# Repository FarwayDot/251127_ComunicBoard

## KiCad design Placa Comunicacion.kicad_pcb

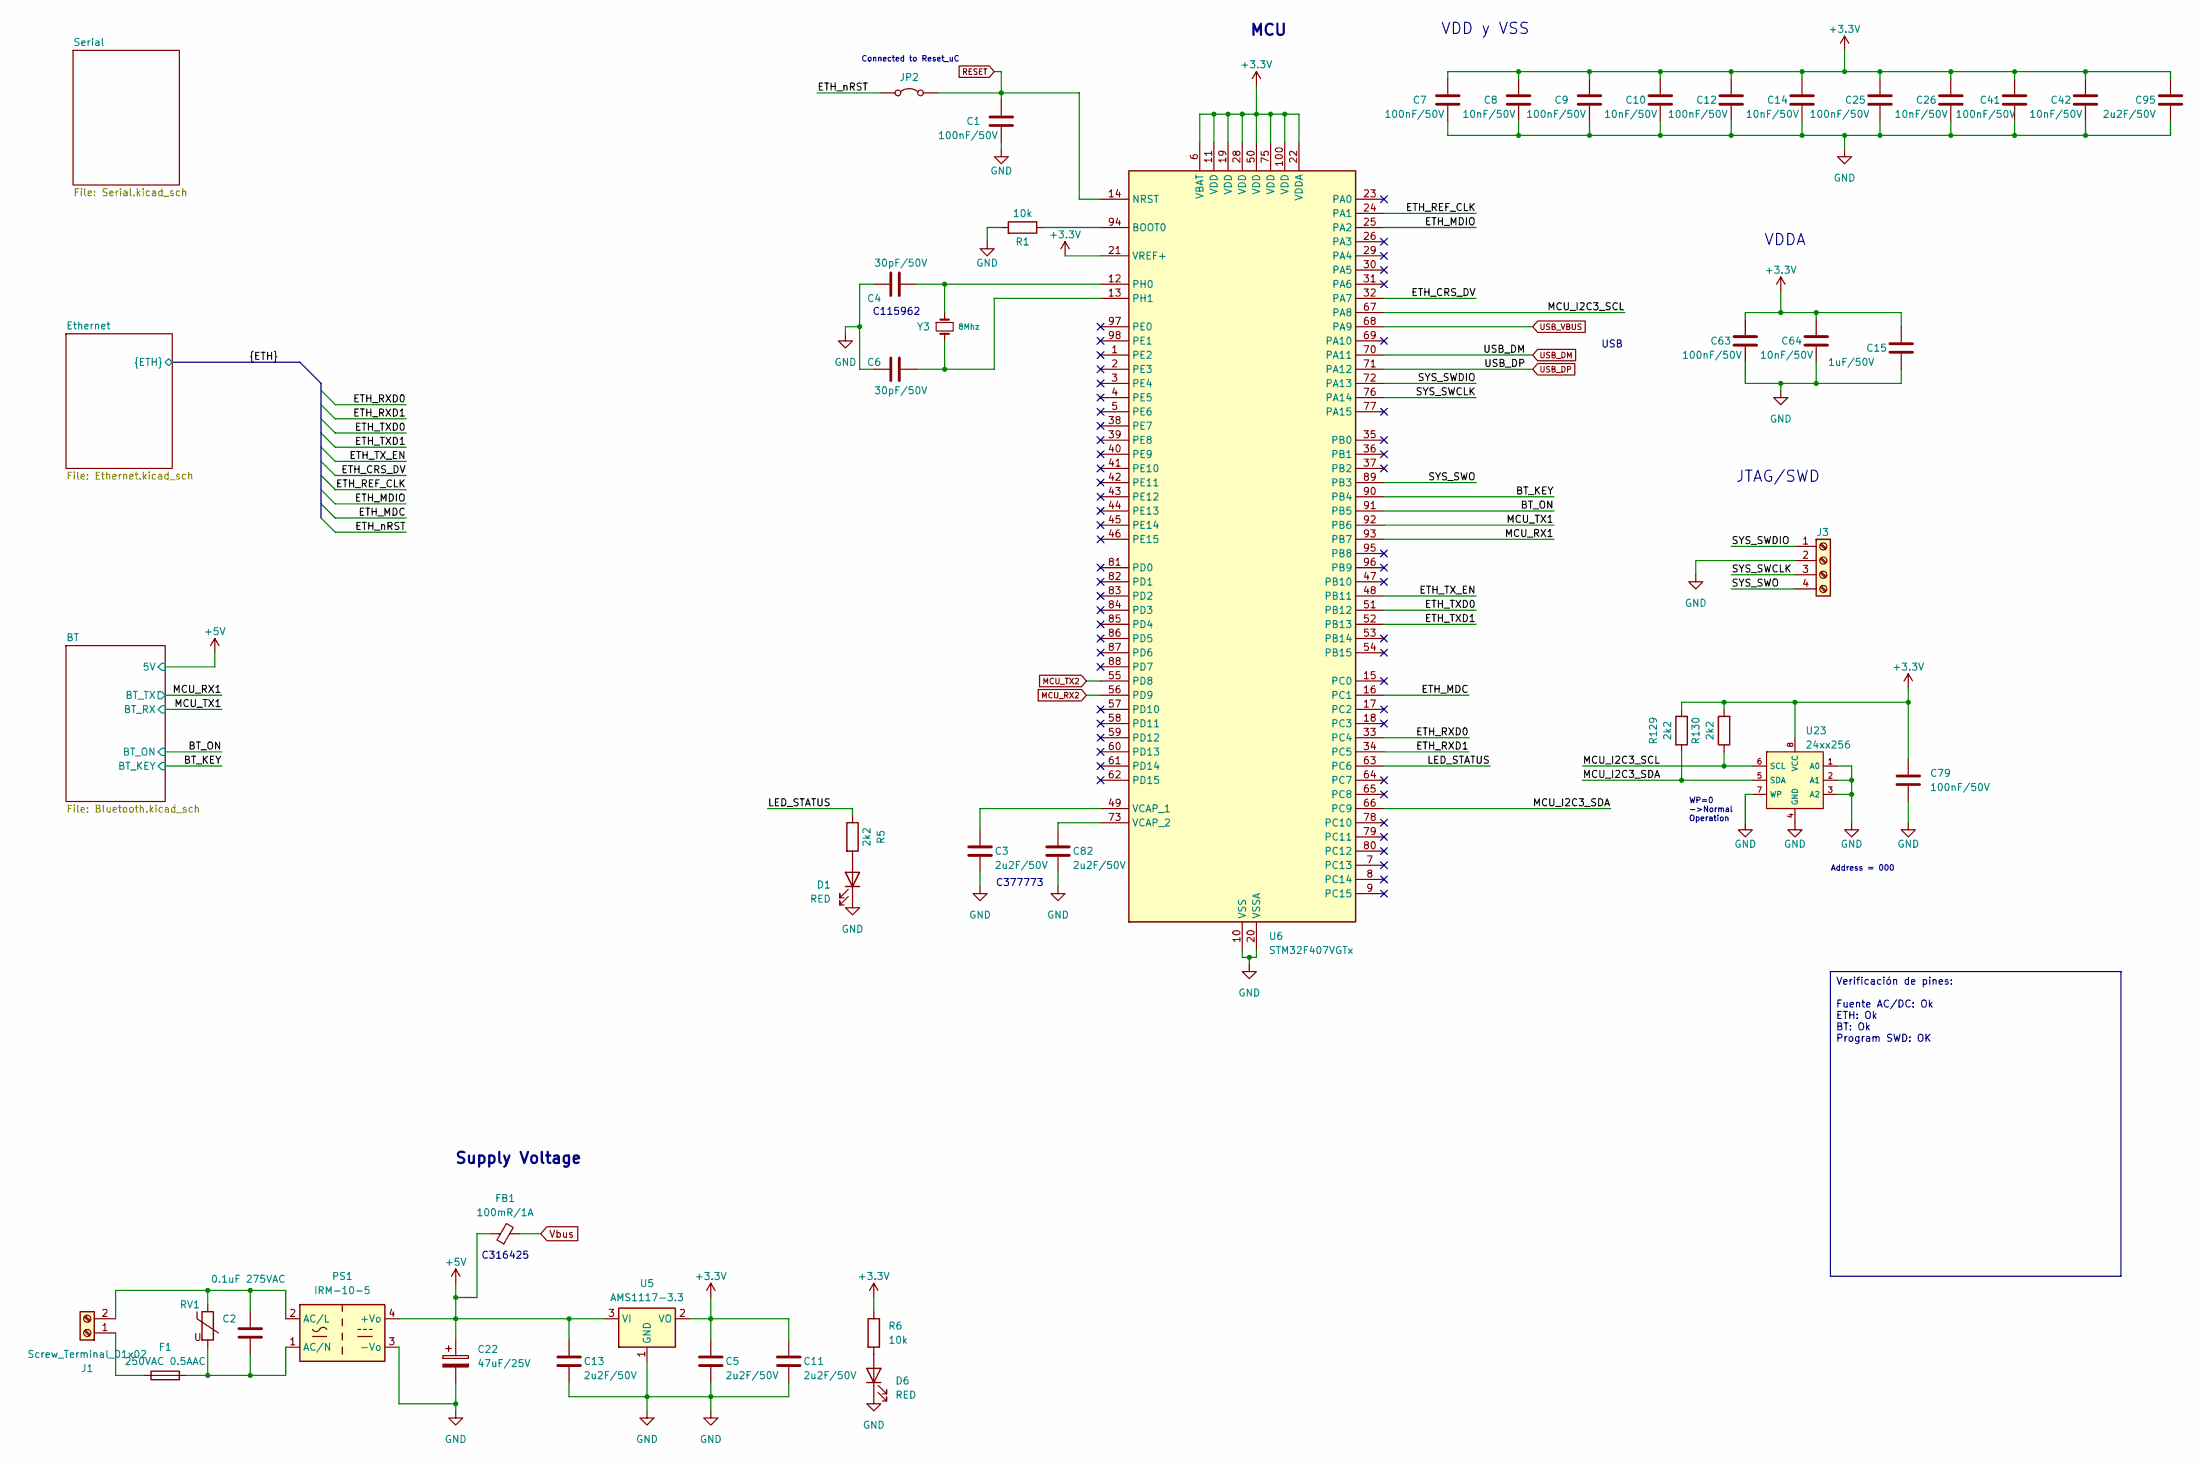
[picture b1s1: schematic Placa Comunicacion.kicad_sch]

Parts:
C1, C7, C9, C12, C25, C41, C63, C79: 100nF/50V; C_0603_1608Metric
C2: 0.1uF 275VAC; C_Rect_L18.0mm_W5.0mm_P15.00mm_FKS3_FKP3
C3, C5, C11, C13, C82, C95: 2u2F/50V; C_0805_2012Metric
C4, C6: 30pF/50V; C_0603_1608Metric
C8, C10, C14, C26, C42, C64: 10nF/50V; C_0603_1608Metric
C15: 1uF/50V; C_0805_2012Metric
C22: 47uF/25V; CP_Radial_D5.0mm_P2.50mm
D1, D6: RED; LED_0805
F1: 250VAC 0.5AAC; Fuseholder_TR5_Littelfuse_No560_No460
FB1: 100mR/1A; L_0805_2012Metric
J1: Screw_Terminal_01x02; DG126_5.0_02P
J3: Screw_Terminal_01x04; PinHeader_1x04_P2.54mm_Vertical
JP2: Jumper_2_Bridged; SolderJumper-2_P1.3mm_Open_Pad1.0x1.5mm
PS1: IRM-10-5; Converter_ACDC_MeanWell_IRM-10-xx_THT
R1, R6: 10k; R_0603_1608Metric
R5, R129, R130: 2k2; R_0603_1608Metric
RV1: RM10D561KD24E100; RV_Disc_D12mm_W5.1mm_P7.5mm
U5: AMS1117-3.3; SOT-223-3_TabPin2
U6: STM32F407VGTx; LQFP-100_14x14mm_P0.5mm
U23: 24xx256; SO-8_3.9x4.9mm_P1.27mm
Y3: 8Mhz; Crystal_SMD_5032-2Pin_5.0x3.2mm

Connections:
+3.3V: C5.1, C7.1, C8.1, C9.1, C10.1, C11.1, C12.1, C14.1, C15.1, C25.1, C26.1, C41.1, C42.1, C63.1, C64.1, C79.1, C95.1, R6.1, R129.2, R130.2, U5.2 (VO), U6.6 (VBAT), U6.11 (VDD), U6.19 (VDD), U6.21 (VREF+), U6.22 (VDDA), U6.28 (VDD), U6.50 (VDD), U6.75 (VDD), U6.100 (VDD), U23.8 (VCC); also elsewhere on the board
+5V: C13.1, C22.1, FB1.1, PS1.4 (+Vo), U5.3 (VI); also elsewhere on the board
/BT_KEY: U6.90 (PB4); also elsewhere on the board
/BT_ON: U6.91 (PB5); also elsewhere on the board
/ETH_CRS_DV: U6.32 (PA7); also elsewhere on the board
/ETH_MDC: U6.16 (PC1); also elsewhere on the board
/ETH_MDIO: U6.25 (PA2); also elsewhere on the board
/ETH_REF_CLK: U6.24 (PA1); also elsewhere on the board
/ETH_RXD0: U6.33 (PC4); also elsewhere on the board
/ETH_RXD1: U6.34 (PC5); also elsewhere on the board
/ETH_TXD0: U6.51 (PB12); also elsewhere on the board
/ETH_TXD1: U6.52 (PB13); also elsewhere on the board
/ETH_TX_EN: U6.48 (PB11); also elsewhere on the board
/ETH_nRST: JP2.1 (A); also elsewhere on the board
/LED_STATUS: R5.1, U6.63 (PC6)
/MCU_I2C3_SCL: R130.1, U6.67 (PA8), U23.6 (SCL)
/MCU_I2C3_SDA: R129.1, U6.66 (PC9), U23.5 (SDA)
/MCU_RX1: U6.93 (PB7); also elsewhere on the board
/MCU_TX1: U6.92 (PB6); also elsewhere on the board
/SYS_SWCLK: J3.3, U6.76 (PA14)
/SYS_SWDIO: J3.1, U6.72 (PA13)
/SYS_SWO: J3.4, U6.89 (PB3)
GND: C1.2, C3.2, C4.2, C5.2, C6.2, C7.2, C8.2, C9.2, C10.2, C11.2, C12.2, C13.2, C14.2, C15.2, C22.2, C25.2, C26.2, C41.2, C42.2, C63.2, C64.2, C79.2, C82.2, C95.2, D1.1 (K), D6.1 (K), J3.2, PS1.3 (-Vo), R1.2, U5.1 (GND), U6.10 (VSS), U6.20 (VSSA), U6.27 (VSS), U6.74 (VSS), U6.99 (VSS), U23.1 (A0), U23.2 (A1), U23.3 (A2), U23.4 (GND), U23.7 (WP); also elsewhere on the board
MCU_RX2: U6.56 (PD9); also elsewhere on the board
MCU_TX2: U6.55 (PD8); also elsewhere on the board
unnamed: D1.2 (A), R5.2
unnamed: D6.2 (A), R6.2
unnamed: F1.1, J1.1
unnamed: C2.1, J1.2, PS1.2 (AC/L), RV1.1
unnamed: C2.2, F1.2, PS1.1 (AC/N), RV1.2
unnamed: R1.1, U6.94 (BOOT0)
unnamed: C4.1, U6.12 (PH0), Y3.1
unnamed: C6.1, U6.13 (PH1), Y3.2
unnamed: C3.1, U6.49 (VCAP_1)
unnamed: C82.1, U6.73 (VCAP_2)
RESET: C1.1, JP2.2 (B), U6.14 (NRST)
USB_DM: U6.70 (PA11); also elsewhere on the board
USB_DP: U6.71 (PA12); also elsewhere on the board
USB_VBUS: U6.68 (PA9); also elsewhere on the board
Vbus: FB1.2; also elsewhere on the board

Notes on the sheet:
C377773
Address = 000
MCU
USB
JTAG/SWD
C316425
Connected to Reset_uC
WP=0 ->Normal Operation
Supply Voltage
C115962
VDD y VSS
VDDA
Verificación de pines: Fuente AC/DC: Ok ETH: Ok BT: Ok Program SWD: OK

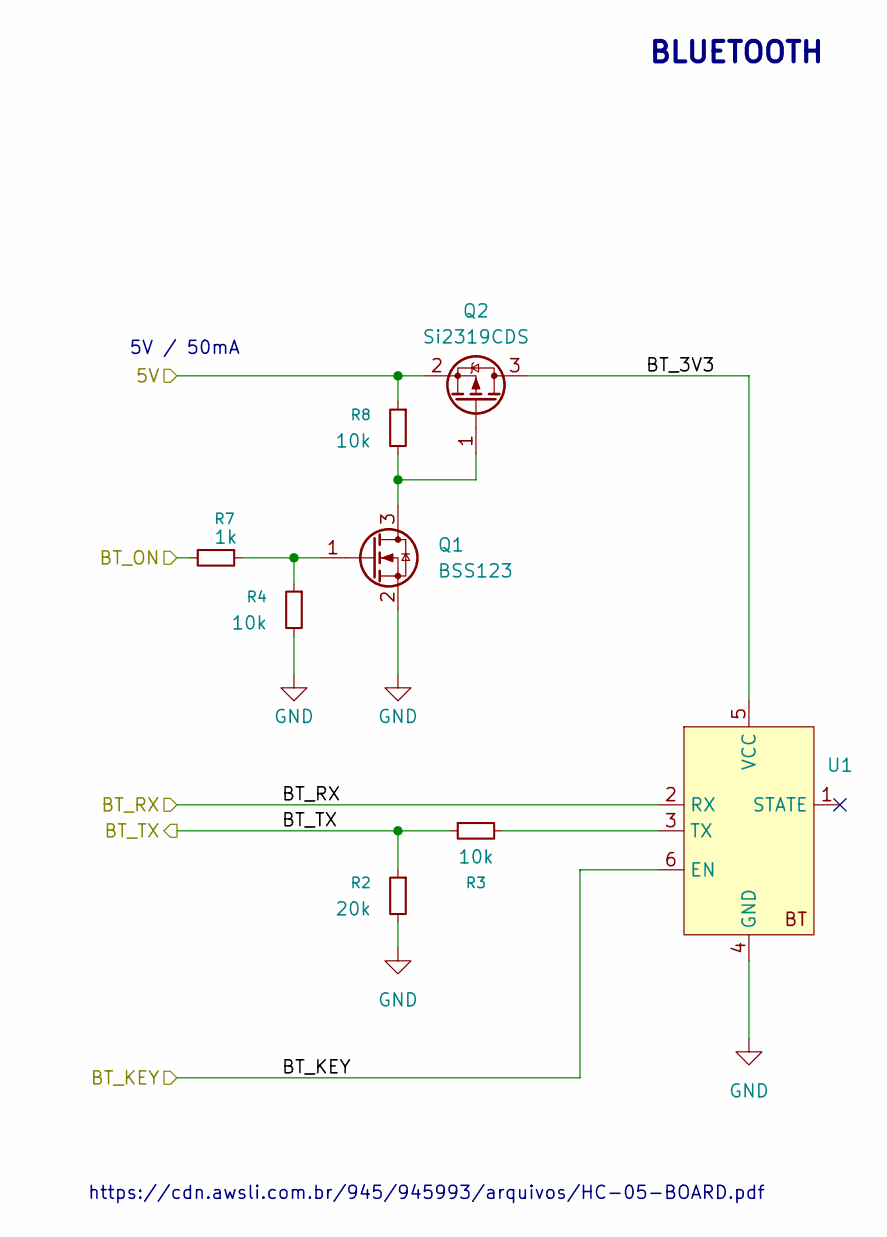
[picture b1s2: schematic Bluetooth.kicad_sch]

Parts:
Q1: BSS123; SOT-23
Q2: Si2319CDS; SOT-23
R2: 20k; R_0603_1608Metric
R3, R4, R8: 10k; R_0603_1608Metric
R7: 1k; R_0603_1608Metric
U1: HC-05

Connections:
+5V: Q2.2 (S), R8.1; also elsewhere on the board
/BT/BT_3V3: Q2.3 (D), U1.5 (VCC)
/BT_KEY: U1.6 (EN); also elsewhere on the board
/BT_ON: R7.2; also elsewhere on the board
/MCU_RX1: R2.1, R3.1; also elsewhere on the board
/MCU_TX1: U1.2 (RX); also elsewhere on the board
GND: Q1.2 (S), R2.2, R4.2, U1.4 (GND); also elsewhere on the board
unnamed: Q1.3 (D), Q2.1 (G), R8.2
unnamed: Q1.1 (G), R4.1, R7.1
unnamed: R3.2, U1.3 (TX)

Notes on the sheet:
https://cdn.awsli.com.br/945/945993/arquivos/HC-05-BOARD.pdf
5V / 50mA
BLUETOOTH

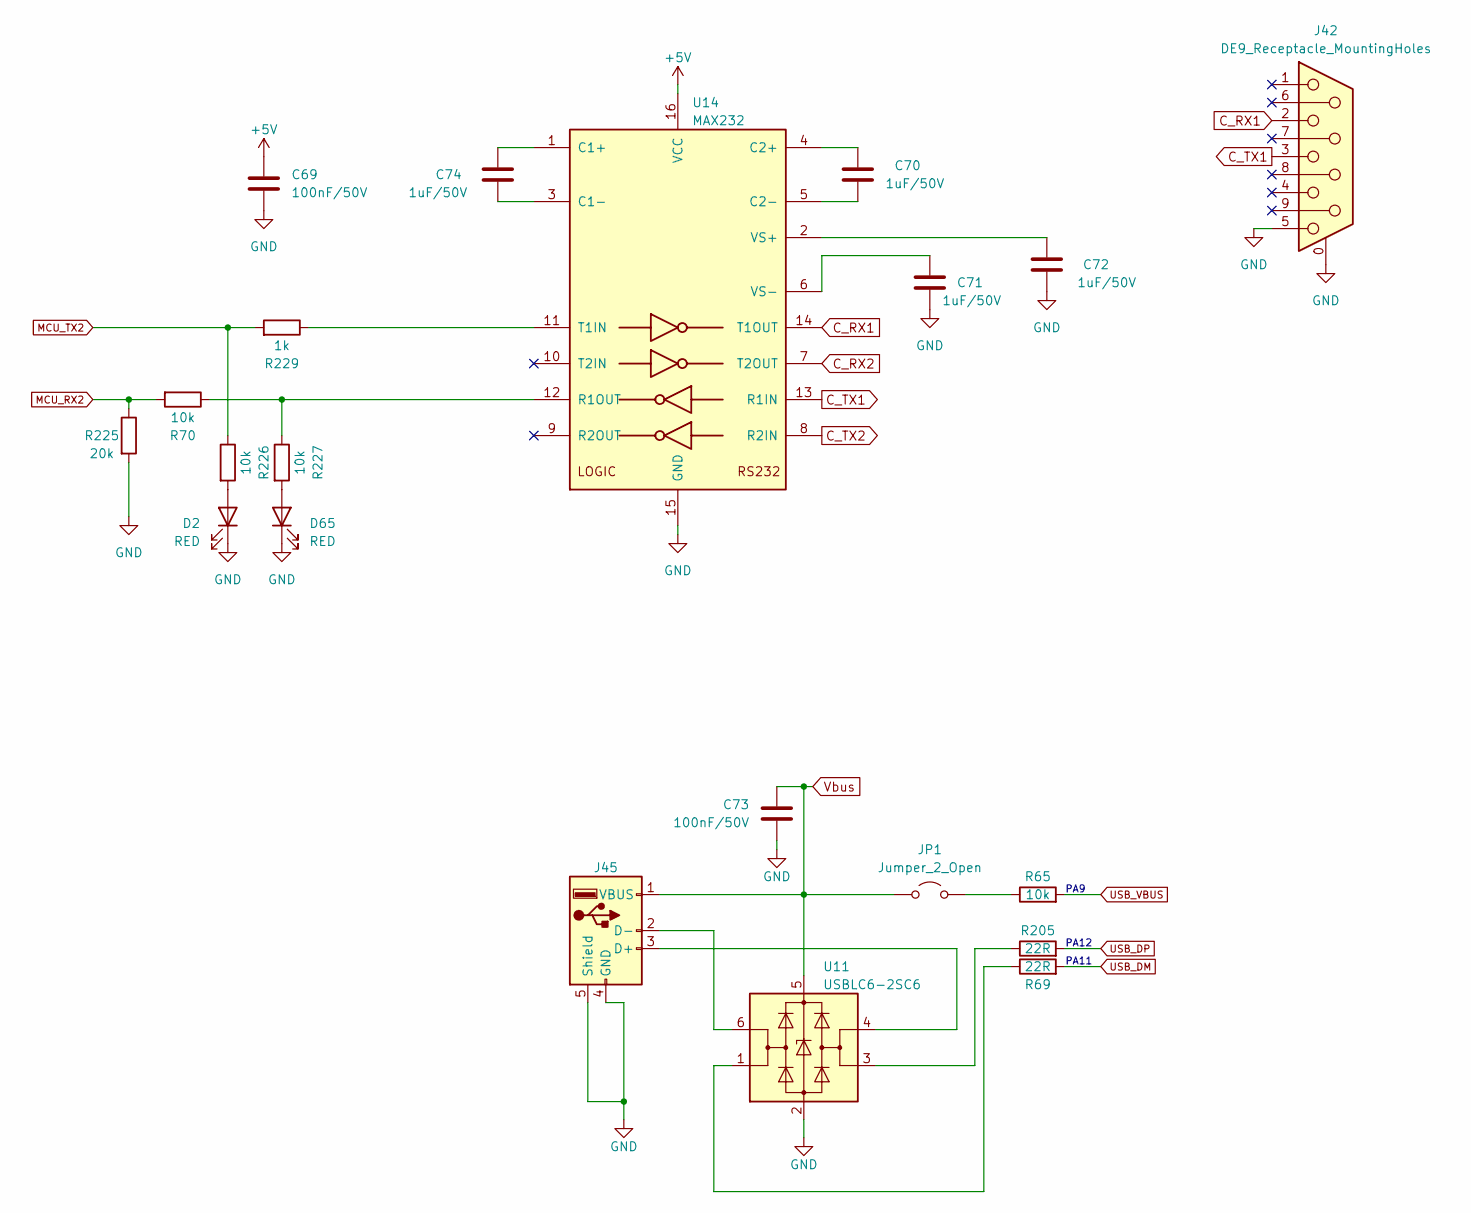
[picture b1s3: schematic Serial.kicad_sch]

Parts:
C69, C73: 100nF/50V; C_0603_1608Metric
C70, C71, C72, C74: 1uF/50V; C_0805_2012Metric
D2, D65: RED; LED_0805
J42: DE9_Receptacle_MountingHoles; DSUB-9_Pins_Horizontal_P2.77x2.84mm_EdgePinOffset7.70mm_Hou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
J45: USB_A_Female_P2.5mm; MOLEX_67329-8020
JP1: Jumper_2_Open; PinHeader_1x02_P2.54mm_Vertical
R65, R70, R226, R227: 10k; R_0603_1608Metric
R69, R205: 22R; R_0603_1608Metric
R225: 20k; R_0603_1608Metric
R229: 1k; R_0603_1608Metric
U11: USBLC6-2SC6; SOT-23-6
U14: MAX232; SOIC-16_3.9x9.9mm_P1.27mm

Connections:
+5V: C69.1, U14.16 (VCC); also elsewhere on the board
C_RX1: J42.2, U14.14 (T1OUT)
C_RX2: U14.7 (T2OUT)
C_TX1: J42.3, U14.13 (R1IN)
C_TX2: U14.8 (R2IN)
GND: C69.2, C71.2, C72.2, C73.2, D2.1 (K), D65.1 (K), J42.0 (PAD), J42.5, J45.4 (GND), J45.5 (Shield), R225.2, U11.2 (GND), U14.15 (GND); also elsewhere on the board
MCU_RX2: R70.2, R225.1; also elsewhere on the board
MCU_TX2: R226.1, R229.2; also elsewhere on the board
unnamed: D2.2 (A), R226.2
unnamed: D65.2 (A), R227.2
unnamed: J45.3 (D+), U11.4 (I/O2)
unnamed: J45.2 (D-), U11.6 (I/O1)
unnamed: JP1.2 (B), R65.1
unnamed: R69.1, U11.1 (I/O1)
unnamed: R205.1, U11.3 (I/O2)
unnamed: C74.1, U14.1 (C1+)
unnamed: C74.2, U14.3 (C1-)
unnamed: C70.1, U14.4 (C2+)
unnamed: C70.2, U14.5 (C2-)
unnamed: R70.1, R227.1, U14.12 (R1OUT)
unnamed: R229.1, U14.11 (T1IN)
unnamed: C72.1, U14.2 (VS+)
unnamed: C71.1, U14.6 (VS-)
USB_DM: R69.2; also elsewhere on the board
USB_DP: R205.2; also elsewhere on the board
USB_VBUS: R65.2; also elsewhere on the board
Vbus: C73.1, J45.1 (VBUS), JP1.1 (A), U11.5 (VBUS); also elsewhere on the board

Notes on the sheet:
PA11
PA9
PA12

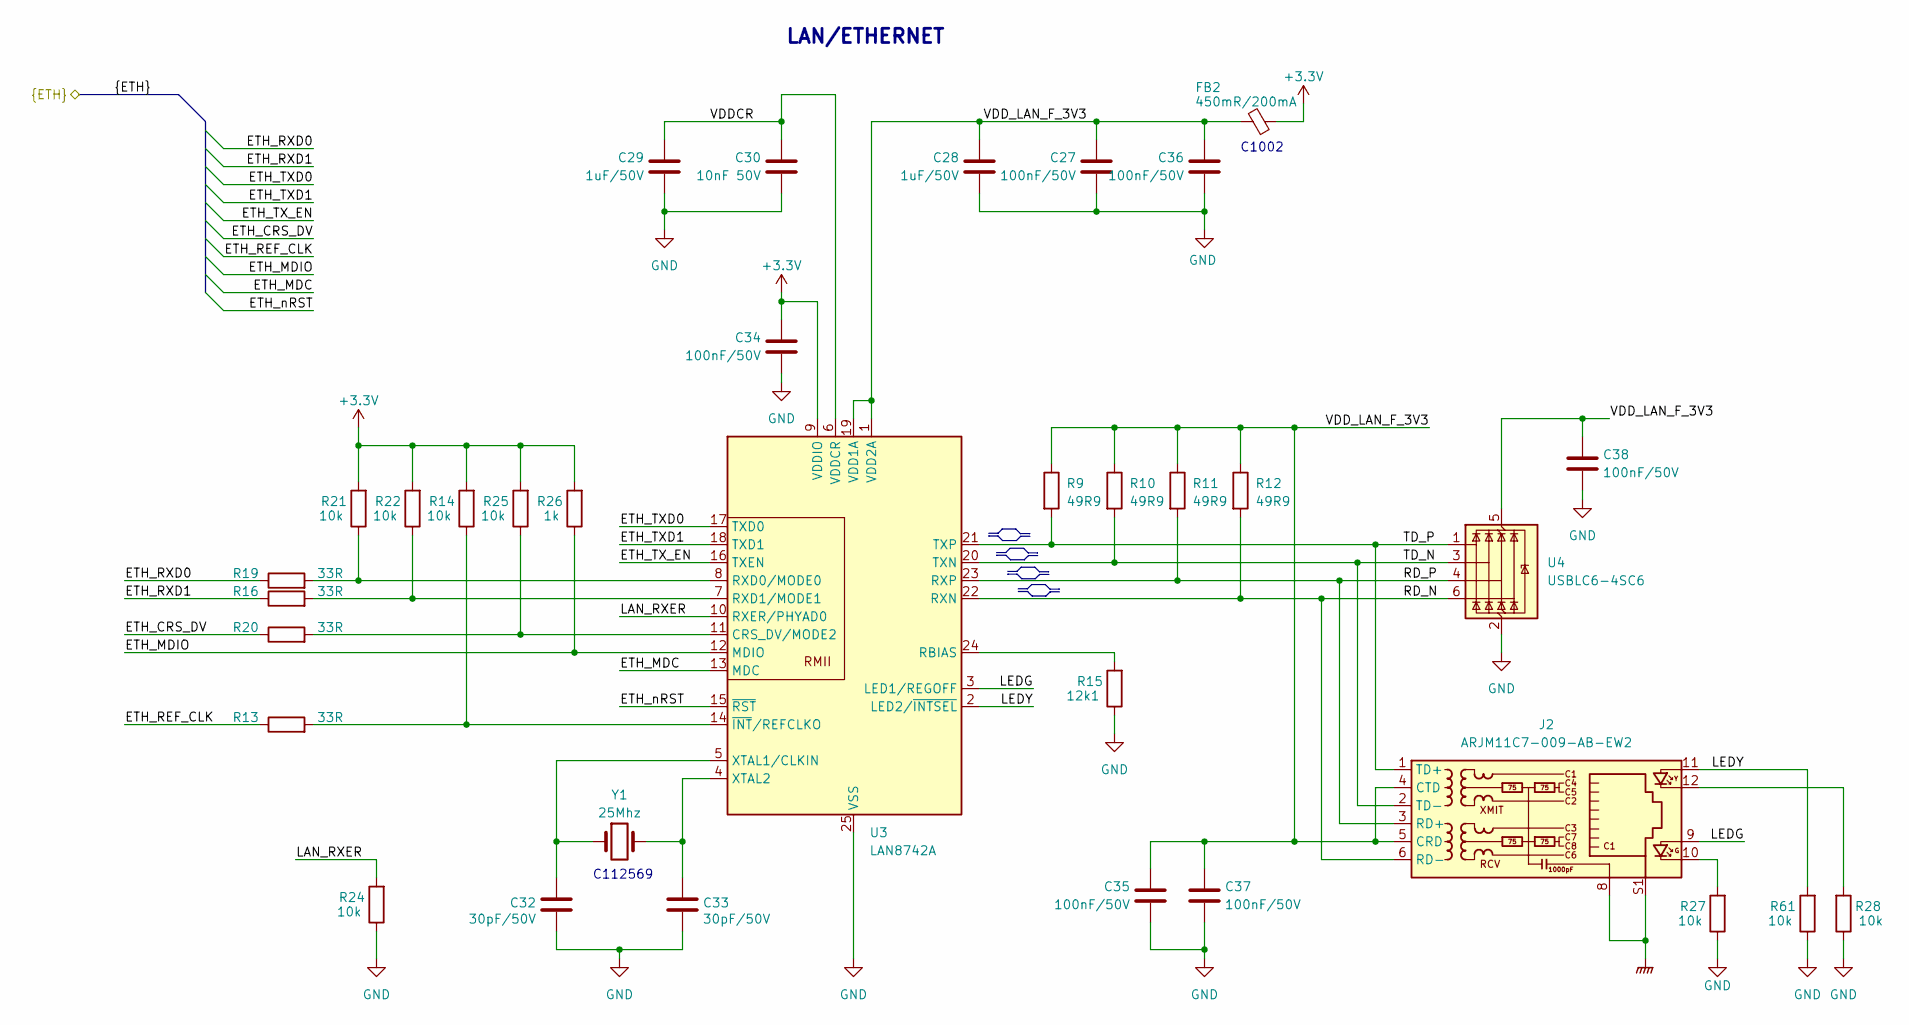
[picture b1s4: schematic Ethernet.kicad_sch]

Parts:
C27, C34, C35, C36, C37, C38: 100nF/50V; C_0603_1608Metric
C28, C29: 1uF/50V; C_0805_2012Metric
C30: 10nF 50V; C_0603_1608Metric
C32, C33: 30pF/50V; C_0603_1608Metric
FB2: 450mR/200mA; L_0603_1608Metric
J2: ARJM11C7-009-AB-EW2; ARJM11C7-009-AB-EW2_Abracon
R9, R10, R11, R12: 49R9; R_0603_1608Metric
R13, R16, R19, R20: 33R; R_0603_1608Metric
R14, R21, R22, R24, R25, R27, R28, R61: 10k; R_0603_1608Metric
R15: 12k1; R_0603_1608Metric
R26: 1k; R_0603_1608Metric
U3: LAN8742A; VQFN-24-1EP_4x4mm_P0.5mm_EP2.5x2.5mm_ThermalVias
U4: USBLC6-4SC6; SOT-23-6
Y1: 25Mhz; Crystal_SMD_5032-2Pin_5.0x3.2mm

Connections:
+3.3V: C34.1, FB2.1, R14.2, R21.2, R22.2, R25.2, R26.2, U3.9 (VDDIO); also elsewhere on the board
/ETH_CRS_DV: R20.1; also elsewhere on the board
/ETH_MDC: U3.13 (MDC); also elsewhere on the board
/ETH_MDIO: R26.1, U3.12 (MDIO); also elsewhere on the board
/ETH_REF_CLK: R13.1; also elsewhere on the board
/ETH_RXD0: R19.1; also elsewhere on the board
/ETH_RXD1: R16.1; also elsewhere on the board
/ETH_TXD0: U3.17 (TXD0); also elsewhere on the board
/ETH_TXD1: U3.18 (TXD1); also elsewhere on the board
/ETH_TX_EN: U3.16 (TXEN); also elsewhere on the board
/ETH_nRST: U3.15 (~RST); also elsewhere on the board
/Ethernet/LAN_RXER: R24.2, U3.10 (RXER/PHYAD0)
/Ethernet/LEDG: J2.9, U3.3 (LED1/REGOFF)
/Ethernet/LEDY: J2.11, R61.2, U3.2 (LED2/~INTSEL)
/Ethernet/RD_N: J2.6 (RD-), R12.2, U3.22 (RXN), U4.6 (I/O4)
/Ethernet/RD_P: J2.3 (RD+), R11.2, U3.23 (RXP), U4.4 (I/O3)
/Ethernet/TD_N: J2.2 (TD-), R10.2, U3.20 (TXN), U4.3 (I/O2)
/Ethernet/TD_P: J2.1 (TD+), R9.2, U3.21 (TXP), U4.1 (I/O1)
/Ethernet/VDDCR: C29.1, C30.1, U3.6 (VDDCR)
/Ethernet/VDD_LAN_F_3V3: C27.1, C28.1, C35.1, C36.1, C37.1, C38.1, FB2.2, J2.4 (CTD), J2.5 (CRD), R9.1, R10.1, R11.1, R12.1, U3.1 (VDD2A), U3.19 (VDD1A), U4.5 (VBUS)
GND: C27.2, C28.2, C29.2, C30.2, C32.2, C33.2, C34.2, C35.2, C36.2, C37.2, C38.2, R15.1, R24.1, R27.1, R28.1, R61.1, U3.25 (VSS), U4.2 (GND); also elsewhere on the board
GNDPWR: J2.8, J2.S1, J2.S2
unnamed: J2.10, R27.2
unnamed: J2.12, R28.2
unnamed: R20.2, R25.1, U3.11 (CRS_DV/MODE2)
unnamed: R15.2, U3.24 (RBIAS)
unnamed: R19.2, R21.1, U3.8 (RXD0/MODE0)
unnamed: R16.2, R22.1, U3.7 (RXD1/MODE1)
unnamed: C32.1, U3.5 (XTAL1/CLKIN), Y1.1
unnamed: C33.1, U3.4 (XTAL2), Y1.2
unnamed: R13.2, R14.1, U3.14 (~INT/REFCLKO)

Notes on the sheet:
LAN/ETHERNET
C1002
C112569

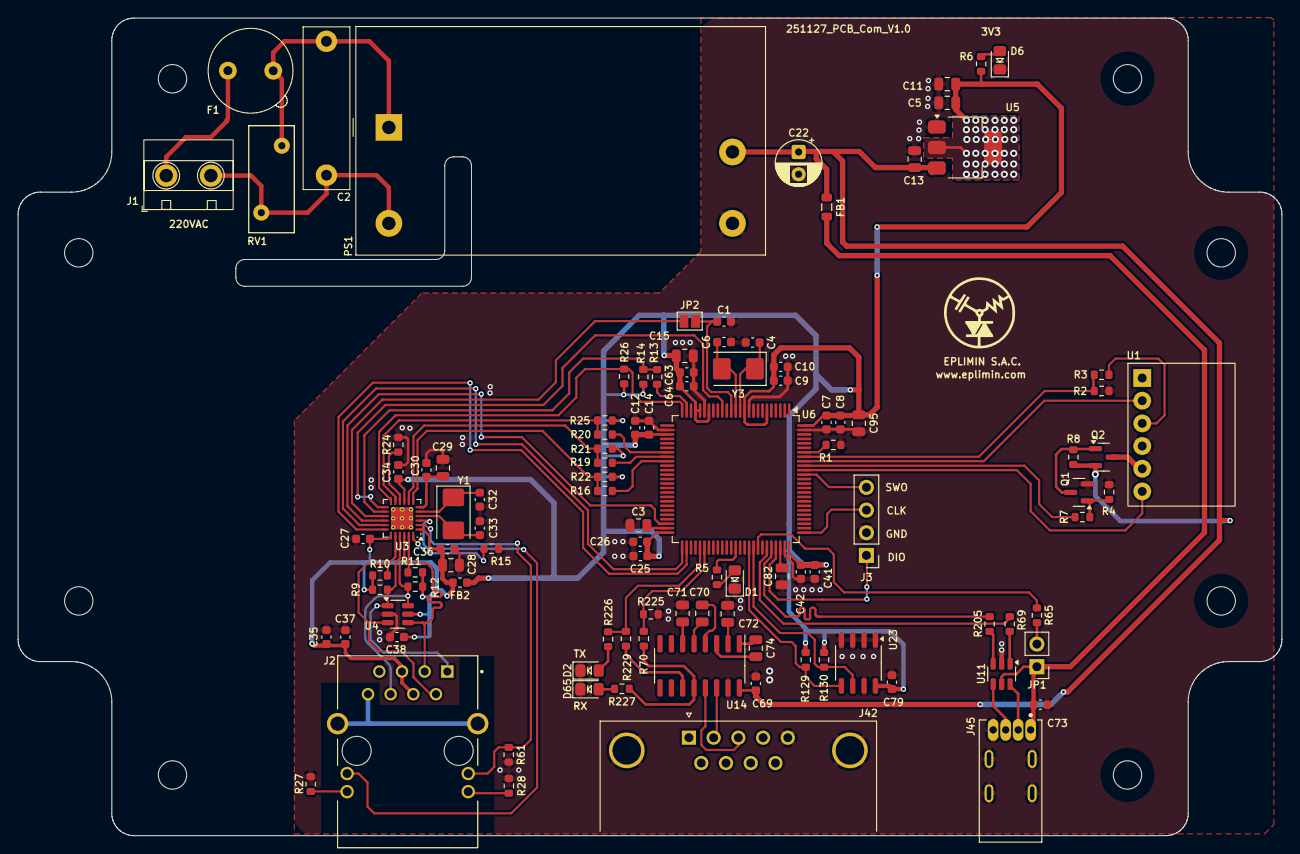
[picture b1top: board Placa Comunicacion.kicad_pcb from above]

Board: 2 copper layers, 141.6 x 91.6 mm, 107 parts (0 on the bottom side), 80 nets.

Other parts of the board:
G1: LOGO

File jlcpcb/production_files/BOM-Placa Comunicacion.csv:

Comment,Designator,Footprint,LCSC,Quantity
450mR/200mA,FB2,L_0603_1608Metric,C1002,1
USBLC6-4SC6,U4,SOT-23-6,C111212,1
25Mhz,Y1,Crystal_SMD_5032-2Pin_5.0x3.2mm,C112569,1
8Mhz,Y3,Crystal_SMD_5032-2Pin_5.0x3.2mm,C115962,1
100nF/50V,"C1,C12,C25,C27,C34,C35,C36,C37,C38,C41,C63,C69,C7,C73,C9",C_0603_1608Metric,C14663,15
24xx256,U23,SO-8_3.9x4.9mm_P1.27mm,C152172,1
30pF/50V,"C32,C33,C4,C6",C_0603_1608Metric,C1658,4
1k,"R229,R26,R7",R_0603_1608Metric,C21190,3
12k1,R15,R_0603_1608Metric,C22864,1
33R,"R13,R16,R19,R20",R_0603_1608Metric,C23140,4
49R9,"R10,R11,R12,R9",R_0603_1608Metric,C23185,4
22R,"R205,R69",R_0603_1608Metric,C23345,2
10k,"R1,R14,R21,R22,R226,R227,R24,R25,R27,R28,R3,R4,R6,R61,R65,R70,R8",R_0603_1608Metric,C25804,17
MAX232,U14,SOIC-16_3.9x9.9mm_P1.27mm,C26860,1
1uF/50V,"C15,C28,C29,C70,C71,C72,C74",C_0805_2012Metric,C28323,7
STM32F407VGTx,U6,LQFP-100_14x14mm_P0.5mm,C28730,1
100mR/1A,FB1,L_0805_2012Metric,C316425,1
2u2F/50V,"C11,C13,C3,C5,C82,C95",C_0805_2012Metric,C377773,6
20k,"R2,R225",R_0603_1608Metric,C4184,2
2k2,"R129,R130,R5",R_0603_1608Metric,C4190,3
AMS1117-3.3,U5,SOT-223-3_TabPin2,C435835,1
10nF/50V,"C10,C14,C26,C30,C42,C64,C8",C_0603_1608Metric,C57112,7
LAN8742A,U3,VQFN-24-1EP_4x4mm_P0.5mm_EP2.5x2.5mm_ThermalVias,C621425,1
USBLC6-2SC6,U11,SOT-23-6,C7519,1
RED,"D1,D2,D6,D65",LED_0805,C84256,4
HC-05,U1,HC-05,,1
Screw_Terminal_01x02,J1,DG126_5.0_02P,,1
Jumper_2_Open,JP1,PinHeader_1x02_P2.54mm_Vertical,,1
Si2319CDS,Q2,SOT-23,,1
IRM-10-5,PS1,Converter_ACDC_MeanWell_IRM-10-xx_THT,,1
250VAC 0.5AAC,F1,Fuseholder_TR5_Littelfuse_No560_No460,,1
USB_A_Female_P2.5mm,J45,MOLEX_67329-8020,,1
0.1uF 275VAC,C2,C_Rect_L18.0mm_W5.0mm_P15.00mm_FKS3_FKP3,,1
RM10D561KD24E100,RV1,RV_Disc_D12mm_W5.1mm_P7.5mm,,1
BSS123,Q1,SOT-23,,1
DE9_Receptacle_MountingHoles,J42,DSUB-9_Pins_Horizontal_P2.77x2.84mm_EdgePinOffset7.70mm_Housed_MountingHolesOffset9.12mm,,1
Jumper_2_Bridged,JP2,SolderJumper-2_P1.3mm_Open_Pad1.0x1.5mm,,1
ARJM11C7-009-AB-EW2,J2,ARJM11C7-009-AB-EW2_Abracon,,1
Screw_Terminal_01x04,J3,PinHeader_1x04_P2.54mm_Vertical,,1
47uF/25V,C22,CP_Radial_D5.0mm_P2.50mm,,1
100nF/50V,C79,C_0603_1608Metric,,1

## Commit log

2025-11-27 Placa de comunicacion para la planta La Merced Revisiones Tecnicas
2025-11-27 Se estandariza algunos atributos: valores, librerias. Se actualiza pcb y se guarda.
2025-11-28 Se estandariza losc omponentes, se cambian algunos valores para evitar gastos adicionales. Se termina y comprueb el part list para jlcpcb
2025-12-04 Se añade led status y eeprom externa. Se actutliza y añade serigrafía a la pcb, se escoge uC de menos flash debido a la escasez del uC planeado, sin embargo, funcionará a recomendacion del programado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
